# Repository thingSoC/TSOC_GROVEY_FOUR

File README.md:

# TSOC_GROVEY_FOUR

The **TSOC_GROVEY_FOUR** allows you to connect [thingSoC](http://thingsoc.github.io/), [Mikrobus](http://www.mikroe.com/mikrobus/), 
and/or [Grove System](http://www.seeedstudio.com/blog/2016/03/09/tutorial-intro-to-grove-connectors-for-arduinoraspberry-pi-projects/) 
Modules all at the same time, either standalone, or with any Processor or Radio module.
This gives you maximum flexiblity for parts selection and reuse. 

The **TSOC_GROVEY_FOUR** uses a Cypress Semiconductor PsoC4, a CY8C4245PVI-482 model in a 28 pin TSSOP package, for easy hand soldering.

The thingSoC "Grovey Series" was designed as "Everyday Electronics", a no-frills, low cost, approach to modular embedded product design.
thingSoC boards are similar in size to most break-out-boards (BOBs), but feature a standardized stacking pinout, as well as an I2C metadata store (EEPROM)
to indicate what peripherals are installed.

[TSOC_GROVEY_FOUR](https://github.com/thingSoC/TSOC_GROVEY_FOUR)

**thingSoC Reference Designs** are example thingSoC implementations that implement
various reference and testing circuits for demonstrating the use of the thingSoC libraries.
These reference designs can serve as starting templates for user designs.

---------------------------------------

## TSOC_GROVEY_FOUR Grove Application Pictures

Add the thingSoC GROVEY_WIFI for wireless measurement and control. This example uses a knob (potentiometer) for input, a water level sensor, a buzzer,  and a pump.
If the system detects water in the basement, it can sound the buzzer and start the pump (as an example...) 

[*TSOC_GROVEY_FOUR*](https://github.com/thingSoC/TSOC_GROVEY_FOUR)

Or use a soil moisture sensor to control when your plants get watered. Add an OLED display to get you measusements.

[*TSOC_GROVEY_FOUR*](https://github.com/thingSoC/TSOC_GROVEY_FOUR)

---------------------------------------

## TSOC_GROVEY_FOUR Mikrobus "Click" Application Pictures

The **TSOC_GROVEY_FOUR** is also compatibile with most [Mikrobus](http://www.mikroe.com/mikrobus/) "Click" peripherals.
now you can mix-and-match Click System peripherals with Grove System peripherals at the same time!

[*TSOC_GROVEY_FOUR*](https://github.com/thingSoC/TSOC_GROVEY_FOUR)

---------------------------------------

## TSOC_GROVEY_FOUR Arduino Sketch Examples

Under the "examples" directory are several Arduino IDE examples for using the TSOC_GROVEY_FOUR board with Arduino IDE.
Using the Arduino "Wire" library for I2C communications, or Arduino "Serial" library for UART communications,
it is simple to control the TSOC_GROVEY_FOUR. Although the TSOC_GROVEY_FOUR uses programmable hardware, the device comes
preprogrammed to act as either an I2C I/O Expander, or a UART command line controlled peripheral. T

```c
 
 coming...

```

---------------------------------------
## TSOC_GROVEY_FOUR Programming

The included UART bootloader allows you to reprogram the PSoC with your own programs,
or to chose from a variety of "recipe" programs available for many applications.

You can reprogram the board using any FTDI USB to UART, or any Grove UART adapter :

In order to reprogram the Cypress PSoC4 device, you will need to download and install the PSoC Creator tool, which includes a serial bootloader host application.

Select Tools -> Bootloader Host 

Then select the hex (cyacd) file that you wish to program, and the COM: port of your device. Proess the "Upload" button to reflash teh device.

[PSoC Creator Bootloader Host](https://github.com/thingSoC/TSOC_GROVEY_FOUR)

---------------------------------------
## Other Applications

The TSOC_GROVEY_FOUR can also drive other devices, such as Servos, Motors, Relays and more.

---------------------------------------

## TSOC_GROVEY_FOUR Status <a name="TSOC_GROVEY_FOUR_status"/>

**08/15/2016:** 
Revision 1.4 - Initial Layout 

**08/20/2016:**
Revision 2.0 - Alpha version

**09/02/2016:**
Revision 3.0 - (WIP) add FTDI, JTAG, and 3.3V/5V voltage select jumper

---------------------------------------
## TSOC_GROVEY_FOUR Model Images

[TSOC_GROVEY_FOUR](https://github.com/thingSoC/TSOC_GROVEY_FOUR)

[TSOC_GROVEY_FOUR](https://github.com/thingSoC/TSOC_GROVEY_FOUR)

---------------------------------------

## TSOC_GROVEY_FOUR Documentation Index <a name="TSOC_GROVEY_FOUR_documentation_index"/>

[TSOC_GROVEY_FOUR Project](http://thingsoc.github.io/projects/TSOC_GROVEY_FOUR.html)

[TSOC_GROVEY_FOUR Hardware](https://github.com/thingSoC/TSOC_GROVEY_FOUR/tree/master/TSOC_GROVEY_FOUR/hardware)

---------------------------------------

## thingSoC Documentation Index <a name="thingSoC_documentation_index"/>

[thingSoC Organization Website](http://thingSoC.github.io)

[thingSoC FAQ - Frequently Asked Questions](http://thingsoc.github.io/support/faq.html)

---------------------------------------

[ 
*thingSoC*](http://thingsoc.github.io)

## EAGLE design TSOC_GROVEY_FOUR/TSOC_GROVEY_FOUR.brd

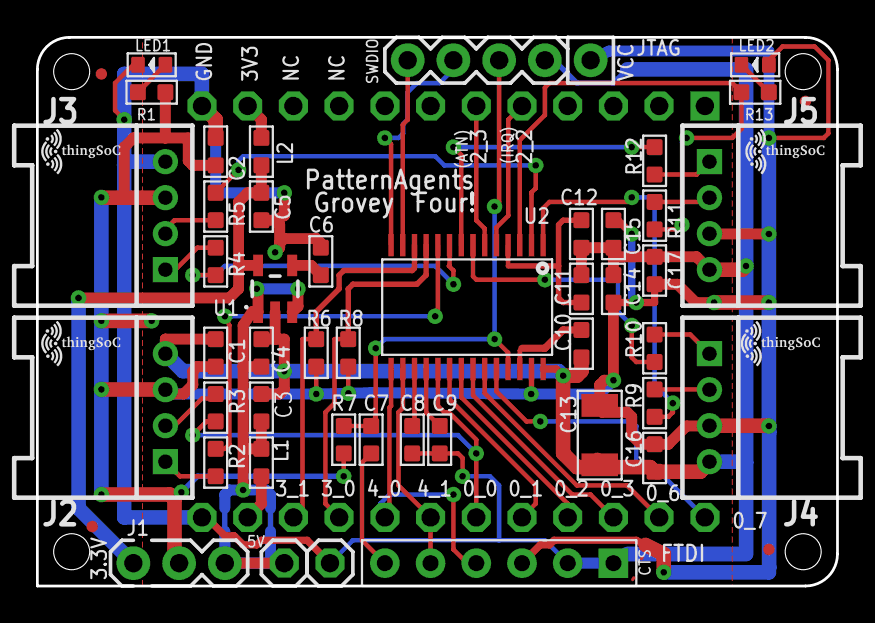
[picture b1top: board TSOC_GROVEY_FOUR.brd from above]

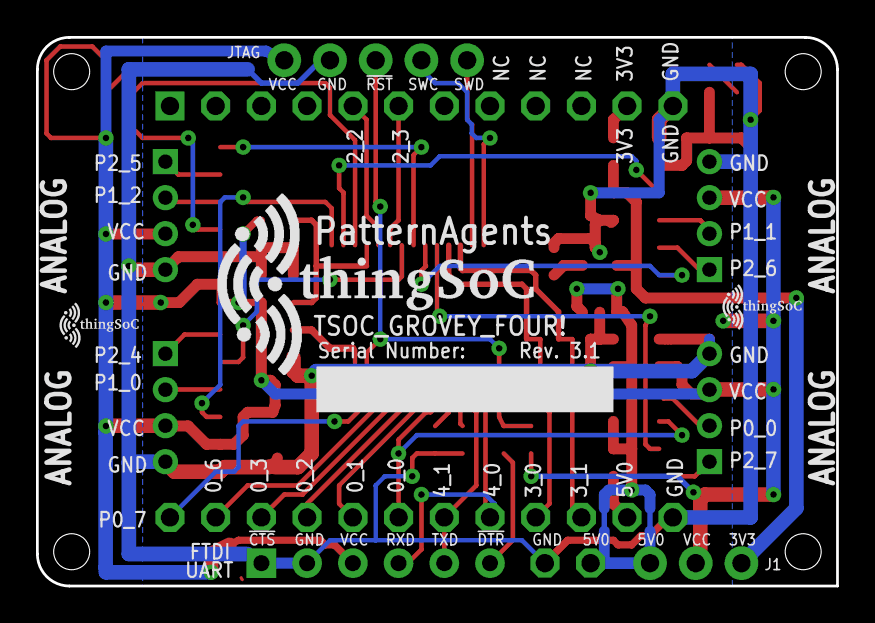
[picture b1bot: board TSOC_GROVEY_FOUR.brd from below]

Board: 2 copper layers, 44.5 x 30.5 mm, 59 parts (3 on the bottom side), 44 nets.

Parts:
5V0: 1X01
$$U$1: TSOC-PCB-SINGLE; TSOC-BB-BRD-DIM
$$U$2, $$U$3: TSOC-LOGO-SMALL; TSOC-LOGO-SML
C1, C2, C4, C6, C7, C11, C15, C16, C17: 100nf; C0603
C3, C5: 10uf; C0603
C8: 2.2nf; C0603
C9: 10nf; C0603
C10, C12, C14: 1uF; C0603
C13: 100uf; C1206
FID1, FID2, FID3, FID4: FIDUCIALUFIDUCIAL; MICRO-FIDUCIAL
FTDI: 6p-2.54; H6-2.54
GND: 1X01
J1: NO; JMP-3-NO-PTH-2.54
J2, J3, J4, J5: 4P-2.0-90D; HW4-2.0-90D
JTAG: JTAG-ISSPMIN; PSOC_JTAG_MINSILK
L1, L2: 120OHM-500MA; L0603
LED1: GREEN-0603; LED-0603
LED2: YELLOW-0603; LED-0603
R1, R2, R3, R4, R5, R9, R10, R11, R12, R13: 1K 1/10W; R0603
R6, R7, R8: 10K 1/10W; R0603
TSOC: TSOC-24-BB; TSOC-BB-S24
U1: 3.3V; SOT23-5
U2: CY8C4XXX-28; SSOP28
U$1, U$3, U$100, U$102: TSOC-LOGO-SMALL; TSOC-LOGO-SML
U$4: TSOC-LOGO; TSOC-LOGO-BLANK
U$101: TSOC-LOGO-LRG

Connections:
3V3: C5.2, J1.1, L2.1, U1.5
5V0: 5V0.1, C3.2, C4.1, J1.3, L1.1, U1.1, U1.3
!URST: C7.1, FTDI.6
!XRES: C7.2, JTAG.3, R7.1, U2.25
A1: J2.1, R2.2
A2: J3.1, R4.2
A3: J4.1, R10.2
A4: J5.1, R12.2
D1: J2.2, R3.2
D2: J3.2, R5.2
D3: J4.2, R9.2
D4: J5.2, R11.2
GND: C1.2, C2.2, C3.1, C4.2, C5.1, C6.2, C8.1, C9.1, C10.1, C11.1, C12.1, C13.2, C14.1, C15.1, C16.2, C17.2, FTDI.1, FTDI.2, GND.1, J2.4, J3.4, J4.4, J5.4, JTAG.2, LED1.-, TSOC.12B, TSOC.12C, U1.2, U2.28
LED1: LED1.+, R1.1
LED2: LED2.-, R13.1
unnamed: C6.1, U1.4
P0_0: R3.1, TSOC.6C, U2.19
P0_1: TSOC.5C, U2.20
P0_2: TSOC.4C, U2.21
P0_3: TSOC.3C, U2.22
P0_6: TSOC.2C, U2.23
P0_7: TSOC.1C, U2.24
P1_0: R9.1, U2.1
P1_1: R5.1, U2.2
P1_2: R11.1, R13.2, U2.3
P1_7: C11.2, C12.2, U2.4
P2_2: TSOC.5B, U2.5
P2_3: TSOC.6B, U2.6
P2_4: R10.1, U2.7
P2_5: R12.1, U2.8
P2_6: R4.1, U2.9
P2_7: R2.1, U2.10
P3_0: R8.1, TSOC.9C, U2.11
P3_1: R6.1, TSOC.10C, U2.12
P3_2: JTAG.5, U2.13
P3_3: JTAG.4, U2.14
P4_0: FTDI.4, TSOC.8C, U2.15
P4_1: FTDI.5, TSOC.7C, U2.16
P4_2: C8.2, U2.17
P4_3: C9.2, U2.18
TSOC_3V3: L2.2, TSOC.11B
TSOC_5V0: L1.2, TSOC.11C
VCC: C1.1, C2.1, C13.1, C14.2, C15.2, C16.1, C17.1, FTDI.3, J1.2, J2.3, J3.3, J4.3, J5.3, JTAG.1, LED2.+, R1.2, R6.2, R7.2, R8.2, U2.27
VCCD: C10.2, U2.26

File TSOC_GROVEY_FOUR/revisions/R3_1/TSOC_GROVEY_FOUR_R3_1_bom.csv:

"Qty";"Value";"Device";"Package";"Parts";"Description";"";
"1";"3.3V";"V_REG_AP2112K-3.3V";"SOT23-5";"U1";"AP2112 - 600mA CMOS LDO Regulator w/ Enable";"";
"1";"CY8C4XXX-28";"CY8C4XXX-28";"SSOP28";"U2";"Cypress PSoC® 4 - Programmable System on Chip,  Cortex-M0 Based";"";
"1";"YELLOW-0603";"SMD-LED-CLEAR-YELLOW(0603)";"LED-0603";"LED2";"304090044";"";
"1";"GREEN-0603";"SMD-LED-CLEAR-GREEN(0603)";"LED-0603";"LED1";"304090043";"";
"2";"120OHM-500MA";"SMD-FERRITE-CHIP-120-OHM-500MA(0603)";"L0603";"L1, L2";"303030001";"";
"10";"1K 1/10W";"SMD-RES-1K-5%-1/10W(0603)";"R0603";"R1, R2, R3, R4, R5, R9, R10, R11, R12, R13";"301010291";"";
"3";"10K 1/10W";"SMD-RES-10K-5%-1/10W(0603)";"R0603";"R6, R7, R8";"301010293";"";
"1";"2.2nf";"CERAMIC-1NF-50V-5%-C0G(0603)";"C0603";"C8";"302010341";"";
"1";"10nf";"CERAMIC-10NF-50V-10%-X7R(0603)";"C0603";"C9";"302010140";"";
"9";"100nf";"CERAMIC-100NF-50V-10%-X7R(0603)";"C0603";"C1, C2, C4, C6, C7, C11, C15, C16, C17";"302010138";"";
"3";"1uF";"CERAMIC-100NF-50V-10%-X7R(0603)";"C0603";"C10, C12, C14";"302010138";"";
"2";"10uf";"CERAMIC-10UF-10V-10%-X5R(0603)";"C0603";"C3, C5";"302010103";"";
"1";"47uf";"CERAMIC-47UF-6.3V-20%-X5R(1206)";"C1206";"C13";"302010183";"";
"4";"4P-2.0-90D";"GROVE-CONNECTOR-DIP-90D(4P-2.0)";"HW4-2.0-90D";"J2, J3, J4, J5";"320110034";"";
"1";"6p-2.54";"DIP-BLACK-MALE-HEADER(6P-2.54)";"H6-2.54";"FTDI";"320020078";"";
"1";"";"M02PTH";"1X02";"5V0, GND";"Header 2 Pin Male";"";
"1";"JTAG-ISSPMIN";"JTAG-ISSPMIN";"PSOC_JTAG_MINSILK";"JTAG";"JTAG-ISSP Programming Connector";"";
"1";"NO";"JMP-3-NO-PTH";"JMP-3-NO-PTH-2.54";"J1";"Three Terminal Jumper - Normally Open";"";
"1";"TSOC-PCB-SINGLE";"TSOC-PCB-SINGLE";"TSOC-BB-BRD-DIM";"$$U$1";"thingSoC PCB Outlines";"";

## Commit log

2016-09-02 initial version
2016-09-03 add product images
2016-09-13 update docs

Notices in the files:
parts and their libraries:
thingSoC: License : http://creativecommons.org/licenses/by-sa/4.0
(Creative Commons 4.0)
PatternAgents-Cypress: License : http://creativecommons.org/licenses/by-sa/3.0
(Creative Commons 3.0)
